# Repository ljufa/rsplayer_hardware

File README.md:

# RSPlayer Hardware

This repository contains the hardware design files for the RSPlayer project, a high-quality audio player. The designs are created in KiCad.

## Design Philosophy

This hardware design prioritizes **modularity** and **DIY-friendliness**. The goal is to provide a flexible platform where enthusiasts can easily swap components, upgrade specific subsystems (like power regulators or output stages), and experiment with different configurations. This open architecture encourages users to tweak the design, test new ideas, and continuously improve the audio performance to match their personal preferences.

## Boards
This repository is structured into several directories, each containing a specific board or a set of related files:

- **control_board_with_amanero**: A control board featuring an Amanero Combo768 USB interface.
- **lpf_ak4497**: Low-pass filter boards designed for the AK4497 DAC datasheet schematics. It includes designs for both `dual` and `dual_mono` configurations.
- [**LT3045_breakout**](https://github.com/PatrickBaus/LT3045_breakout.git): A modular breakout board for LT3042/LT3045 ultra-low noise regulators, used as drop-in replacements for 78xx series regulators.
- [**rsplayer_hardware_docs_private**](https://github.com/ljufa/rsplayer_hardware_docs_private.git): Contains external datasheets for various components used in the project. (this is private due to copyright)
- **MyLibrary.pretty**: A custom KiCad footprint library for this project.

## Features & Benefits

### Core Control & Interface
*   **MCU:** Powered by the **Raspberry Pi Pico (RP2040)**, providing robust system management, user interface control, and configuration logic. [**Firmware is here**](https://github.com/ljufa/rsplayer_firmware.git). 
*   **USB Audio:** Dedicated socket for **Amanero Combo384/Combo768** USB interfaces, supporting high-resolution PCM and DSD playback.
*   **User Interface:** Supports a Rotary Encoder for volume/navigation, IR Receiver (TSOP312) for remote control, and headers for LCD/OLED display integration.

### High-Fidelity Audio Design
*   **Galvanic Isolation:** Full isolation between the digital control logic (Pico/USB) and the sensitive DAC/Audio circuitry. Uses high-speed isolators (e.g., IL715E, ADuM1250) to eliminate ground loops and prevent digital noise from affecting audio quality.
*   **Hardware Muting:** Relay-based output muting protection to prevent audible pops and clicks during power cycles or sample rate changes.
*   **I2S Source Switching:** Features an intelligent I2S switching circuit using dual **74AC573** Octal Latches. This setup acts as a high-speed multiplexer, allowing seamless selection between the **Amanero USB interface (Source B)** and the **Optical/TOSLINK Input (Source A)**, controlled directly by the Raspberry Pi Pico.
*   **I2S & DSD Support:** Native handling of I2S and DSD signals routed directly to the DAC interface.

### Advanced Power Management
*   **Ultra-Low Noise Regulation:** Critically sensitive DAC stages are powered by modular **LT3042/LT3045** regulators. These are implemented as separate breakout boards (based on the `LT3045_breakout` design) acting as high-performance drop-in replacements for standard regulators, providing industry-leading low noise (0.8µVrms) and ultra-high PSRR.
*   **Multi-Rail Linear PSU:** On-board rectification and regulation generating separate clean rails for digital (3.3V), analog, and op-amp stages.
*   **Smart Power Control:** Relay-controlled AC mains switching allows for standby modes and remote power-on capabilities.

## Schematics

## PCB

## Future Roadmap
The project is evolving to become a universal high-fidelity audio platform. Planned improvements include:
*   **Expanded Interface Support:** Adding compatibility for additional **USB-to-I2S** boards beyond the Amanero series.
*   **Universal DAC Support:** Developing adapters and firmware logic to support a wider variety of **DAC chips and boards** (e.g., ESS Sabre, Burr-Brown), allowing users to choose their preferred sound signature.

## Related Projects
The RSPlayer is a multi-repository project:

- [**rsplayer**](https://github.com/ljufa/rsplayer.git): The main music player software running on PC or SBC.
- [**rsplayer_firmware**](https://github.com/ljufa/rsplayer_firmware.git): Firmware for MCU on this board. 

## License
This project is licensed under the MIT License. See the [LICENSE](LICENSE) file for details.

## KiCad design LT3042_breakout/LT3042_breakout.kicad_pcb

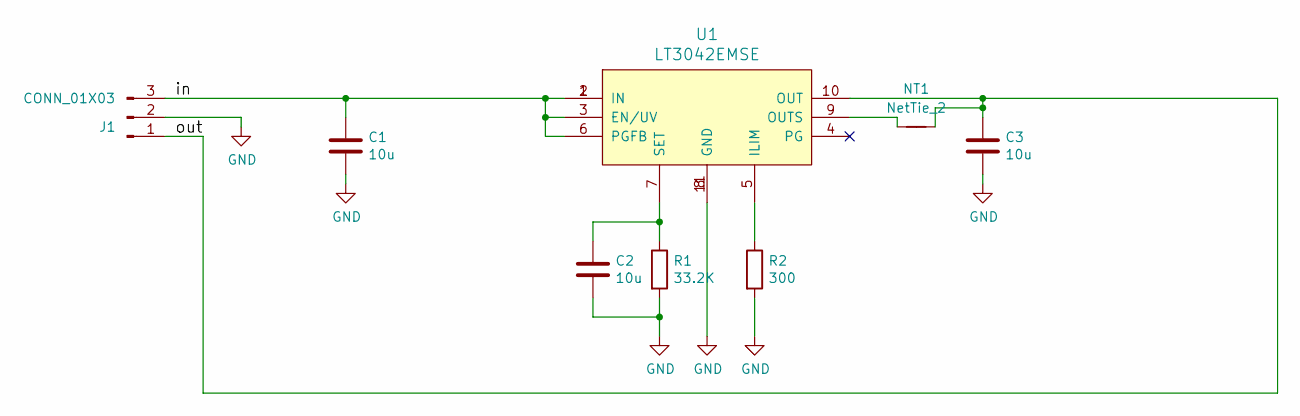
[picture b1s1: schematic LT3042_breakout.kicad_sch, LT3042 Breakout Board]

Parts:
C1, C2, C3: 10u; C_0603_1608Metric
J1: CONN_01X03; PinHeader_1x03_P2.54mm_Horizontal
NT1: NetTie_2; NetTie-2_SMD_Pad0.2mm
R1: 33.2K; R_0603_1608Metric
R2: 300; R_0603_1608Metric
U1: LT3042EMSE; MSOP-10-1EP_3x3mm_P0.5mm_EP1.68x1.88mm_ThermalVias

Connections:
/in: C1.1, J1.3, U1.1 (IN), U1.2 (IN), U1.3 (EN/UV), U1.6 (PGFB)
/out: C3.1, J1.1, NT1.2, U1.10 (OUT)
GND: C1.2, C2.2, C3.2, J1.2, R1.2, R2.2, U1.8 (GND), U1.11
unnamed: R2.1, U1.5 (ILIM)
unnamed: NT1.1, U1.9 (OUTS)
unnamed: C2.1, R1.1, U1.7 (SET)

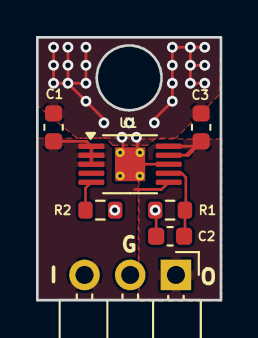
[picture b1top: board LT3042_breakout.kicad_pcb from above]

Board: 2 copper layers, 10.2 x 14.6 mm, 8 parts (0 on the bottom side), 6 nets.

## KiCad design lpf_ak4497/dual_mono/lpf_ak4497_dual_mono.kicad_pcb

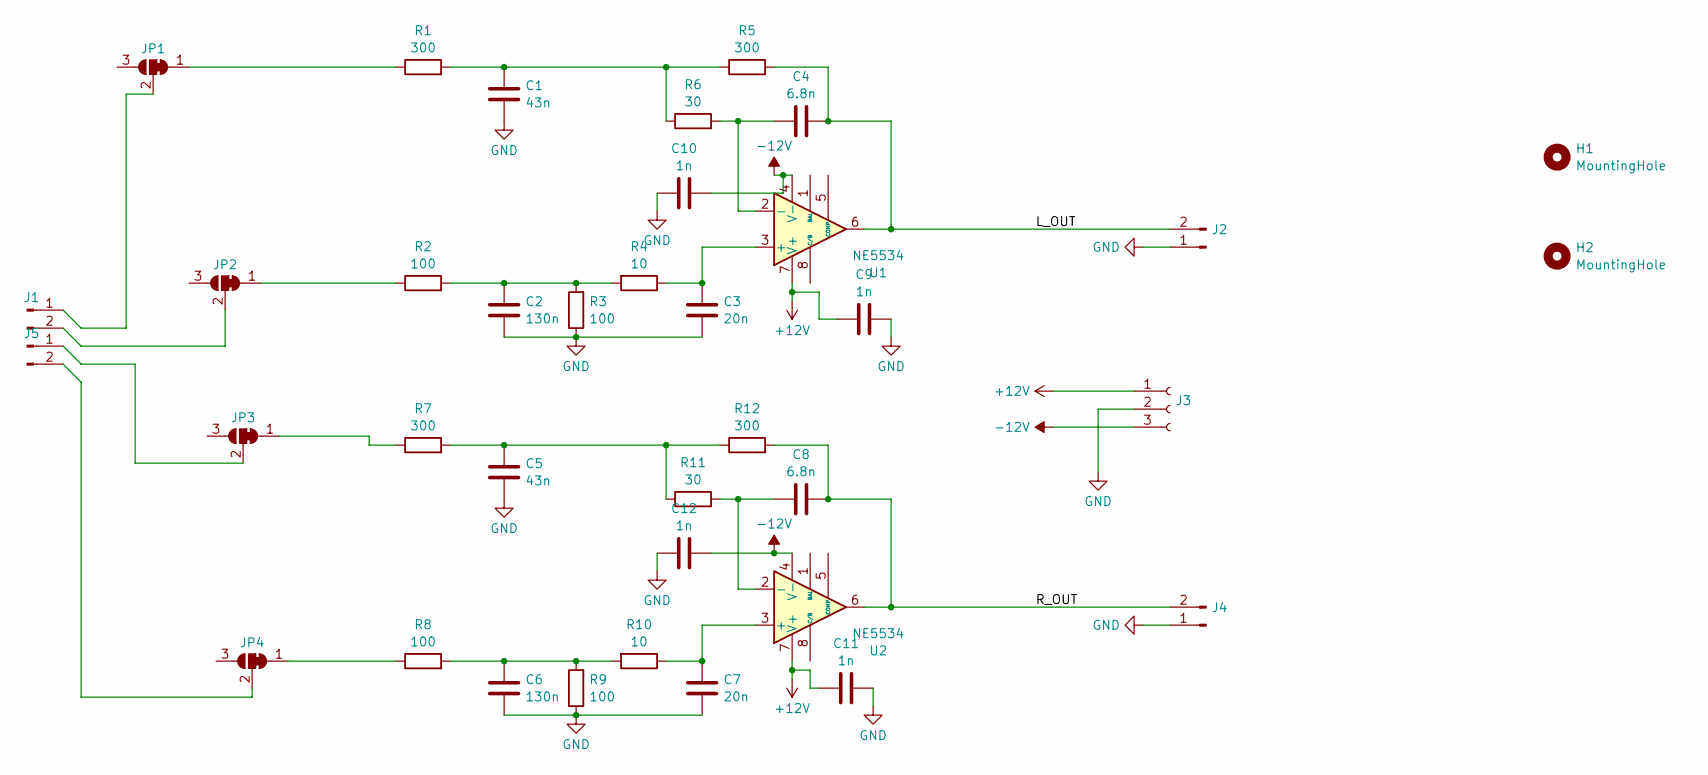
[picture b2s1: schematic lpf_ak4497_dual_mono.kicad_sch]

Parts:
C1, C5: 43n; C_1206_3216Metric_Pad1.33x1.80mm_HandSolder
C2, C6: 130n; C_1206_3216Metric_Pad1.33x1.80mm_HandSolder
C3, C7: 20n; C_1206_3216Metric_Pad1.33x1.80mm_HandSolder
C4, C8: 6.8n; C_1206_3216Metric_Pad1.33x1.80mm_HandSolder
C9, C10, C11, C12: 1n; C_0603_1608Metric_Pad1.08x0.95mm_HandSolder
H1, H2: MountingHole; MountingHole_3.2mm_M3
J1, J2, J4, J5: Conn_01x02_Pin; PinHeader_1x02_P2.54mm_Vertical
J3: Conn_01x03_Socket; PinHeader_1x03_P2.54mm_Vertical
JP1, JP2, JP3, JP4: SolderJumper-3_P1.3mm_Bridged2Bar12_RoundedPad1.0x1.5mm
R1, R5, R7, R12: 300; R_1206_3216Metric_Pad1.30x1.75mm_HandSolder
R2, R3, R8, R9: 100; R_1206_3216Metric_Pad1.30x1.75mm_HandSolder
R4, R10: 10; R_1206_3216Metric_Pad1.30x1.75mm_HandSolder
R6, R11: 30; R_1206_3216Metric_Pad1.30x1.75mm_HandSolder
U1, U2: NE5534; DIP-8_W7.62mm_Socket

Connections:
+12V: C9.2, C11.2, J3.1, U1.7 (V+), U2.7 (V+)
-12V: C10.1, C12.1, J3.3, U1.4 (V-), U2.4 (V-)
/L_OUT: C4.2, J2.2, R5.2, U1.6
/R_OUT: C8.2, J4.2, R12.2, U2.6
GND: C1.2, C2.2, C3.2, C5.2, C6.2, C7.2, C9.1, C10.2, C11.1, C12.2, J2.1, J3.2, J4.1, R3.1, R9.1
unnamed: C1.1, R1.2, R5.1, R6.1
unnamed: C2.1, R2.2, R3.2, R4.2
unnamed: C5.1, R7.2, R11.1, R12.1
unnamed: C6.1, R8.2, R9.2, R10.2
unnamed: J1.1, JP1.2 (C)
unnamed: J1.2, JP2.2 (C)
unnamed: J5.1, JP3.2 (C)
unnamed: J5.2, JP4.2 (C)
unnamed: JP1.1 (A), R1.1
unnamed: JP2.1 (A), R2.1
unnamed: JP3.1 (A), R7.1
unnamed: JP4.1 (A), R8.1
unnamed: C3.1, R4.1, U1.3 (+)
unnamed: C4.1, R6.2, U1.2 (-)
unnamed: C7.1, R10.1, U2.3 (+)
unnamed: C8.1, R11.2, U2.2 (-)

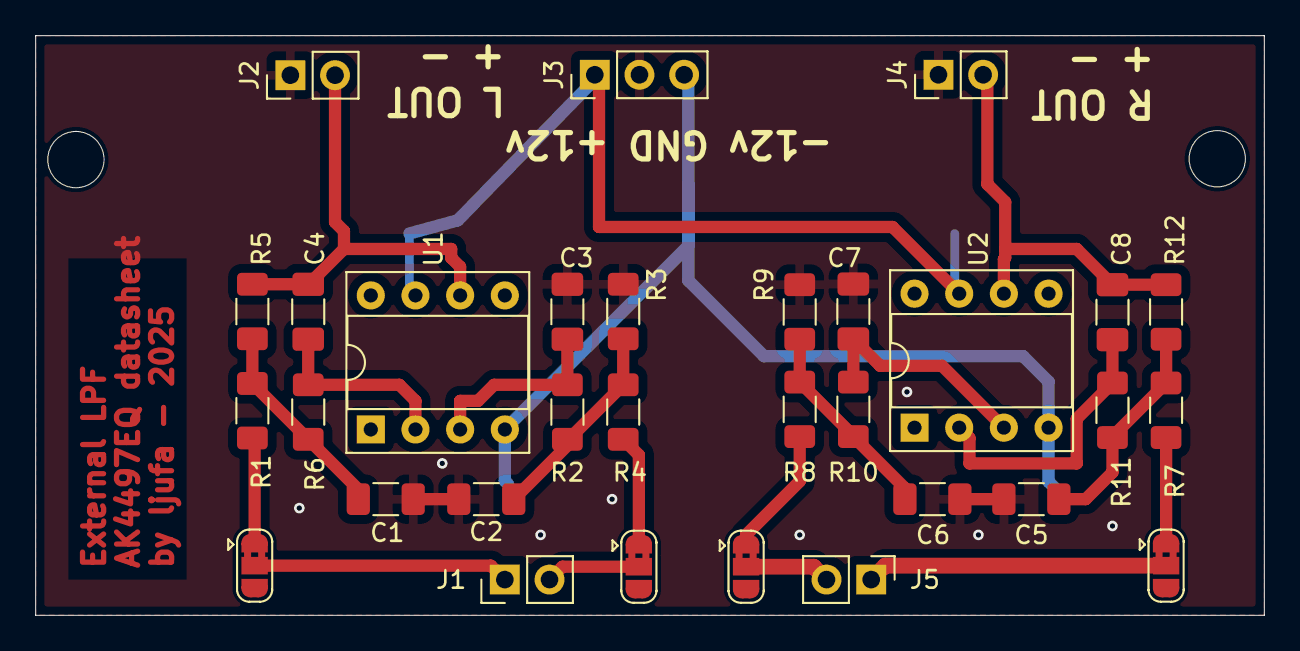
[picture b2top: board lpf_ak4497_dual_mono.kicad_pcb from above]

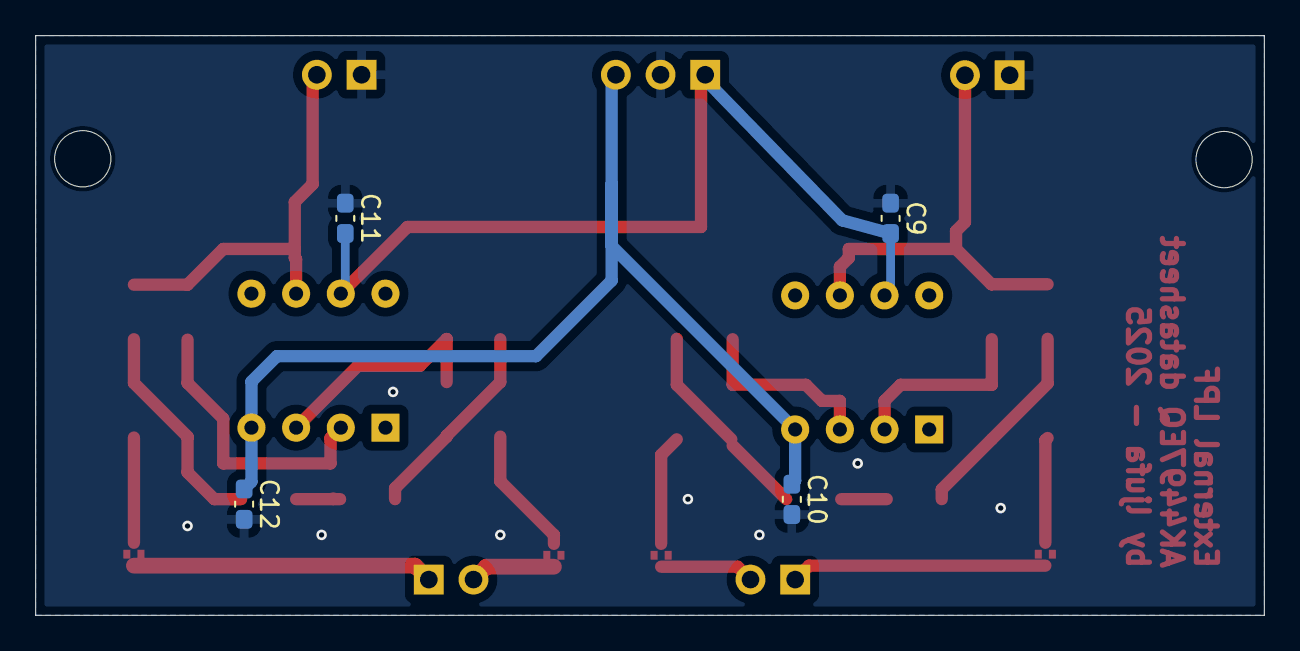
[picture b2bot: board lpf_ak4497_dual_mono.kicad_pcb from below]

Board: 2 copper layers, 69.9 x 33.0 mm, 37 parts (4 on the bottom side), 21 nets.

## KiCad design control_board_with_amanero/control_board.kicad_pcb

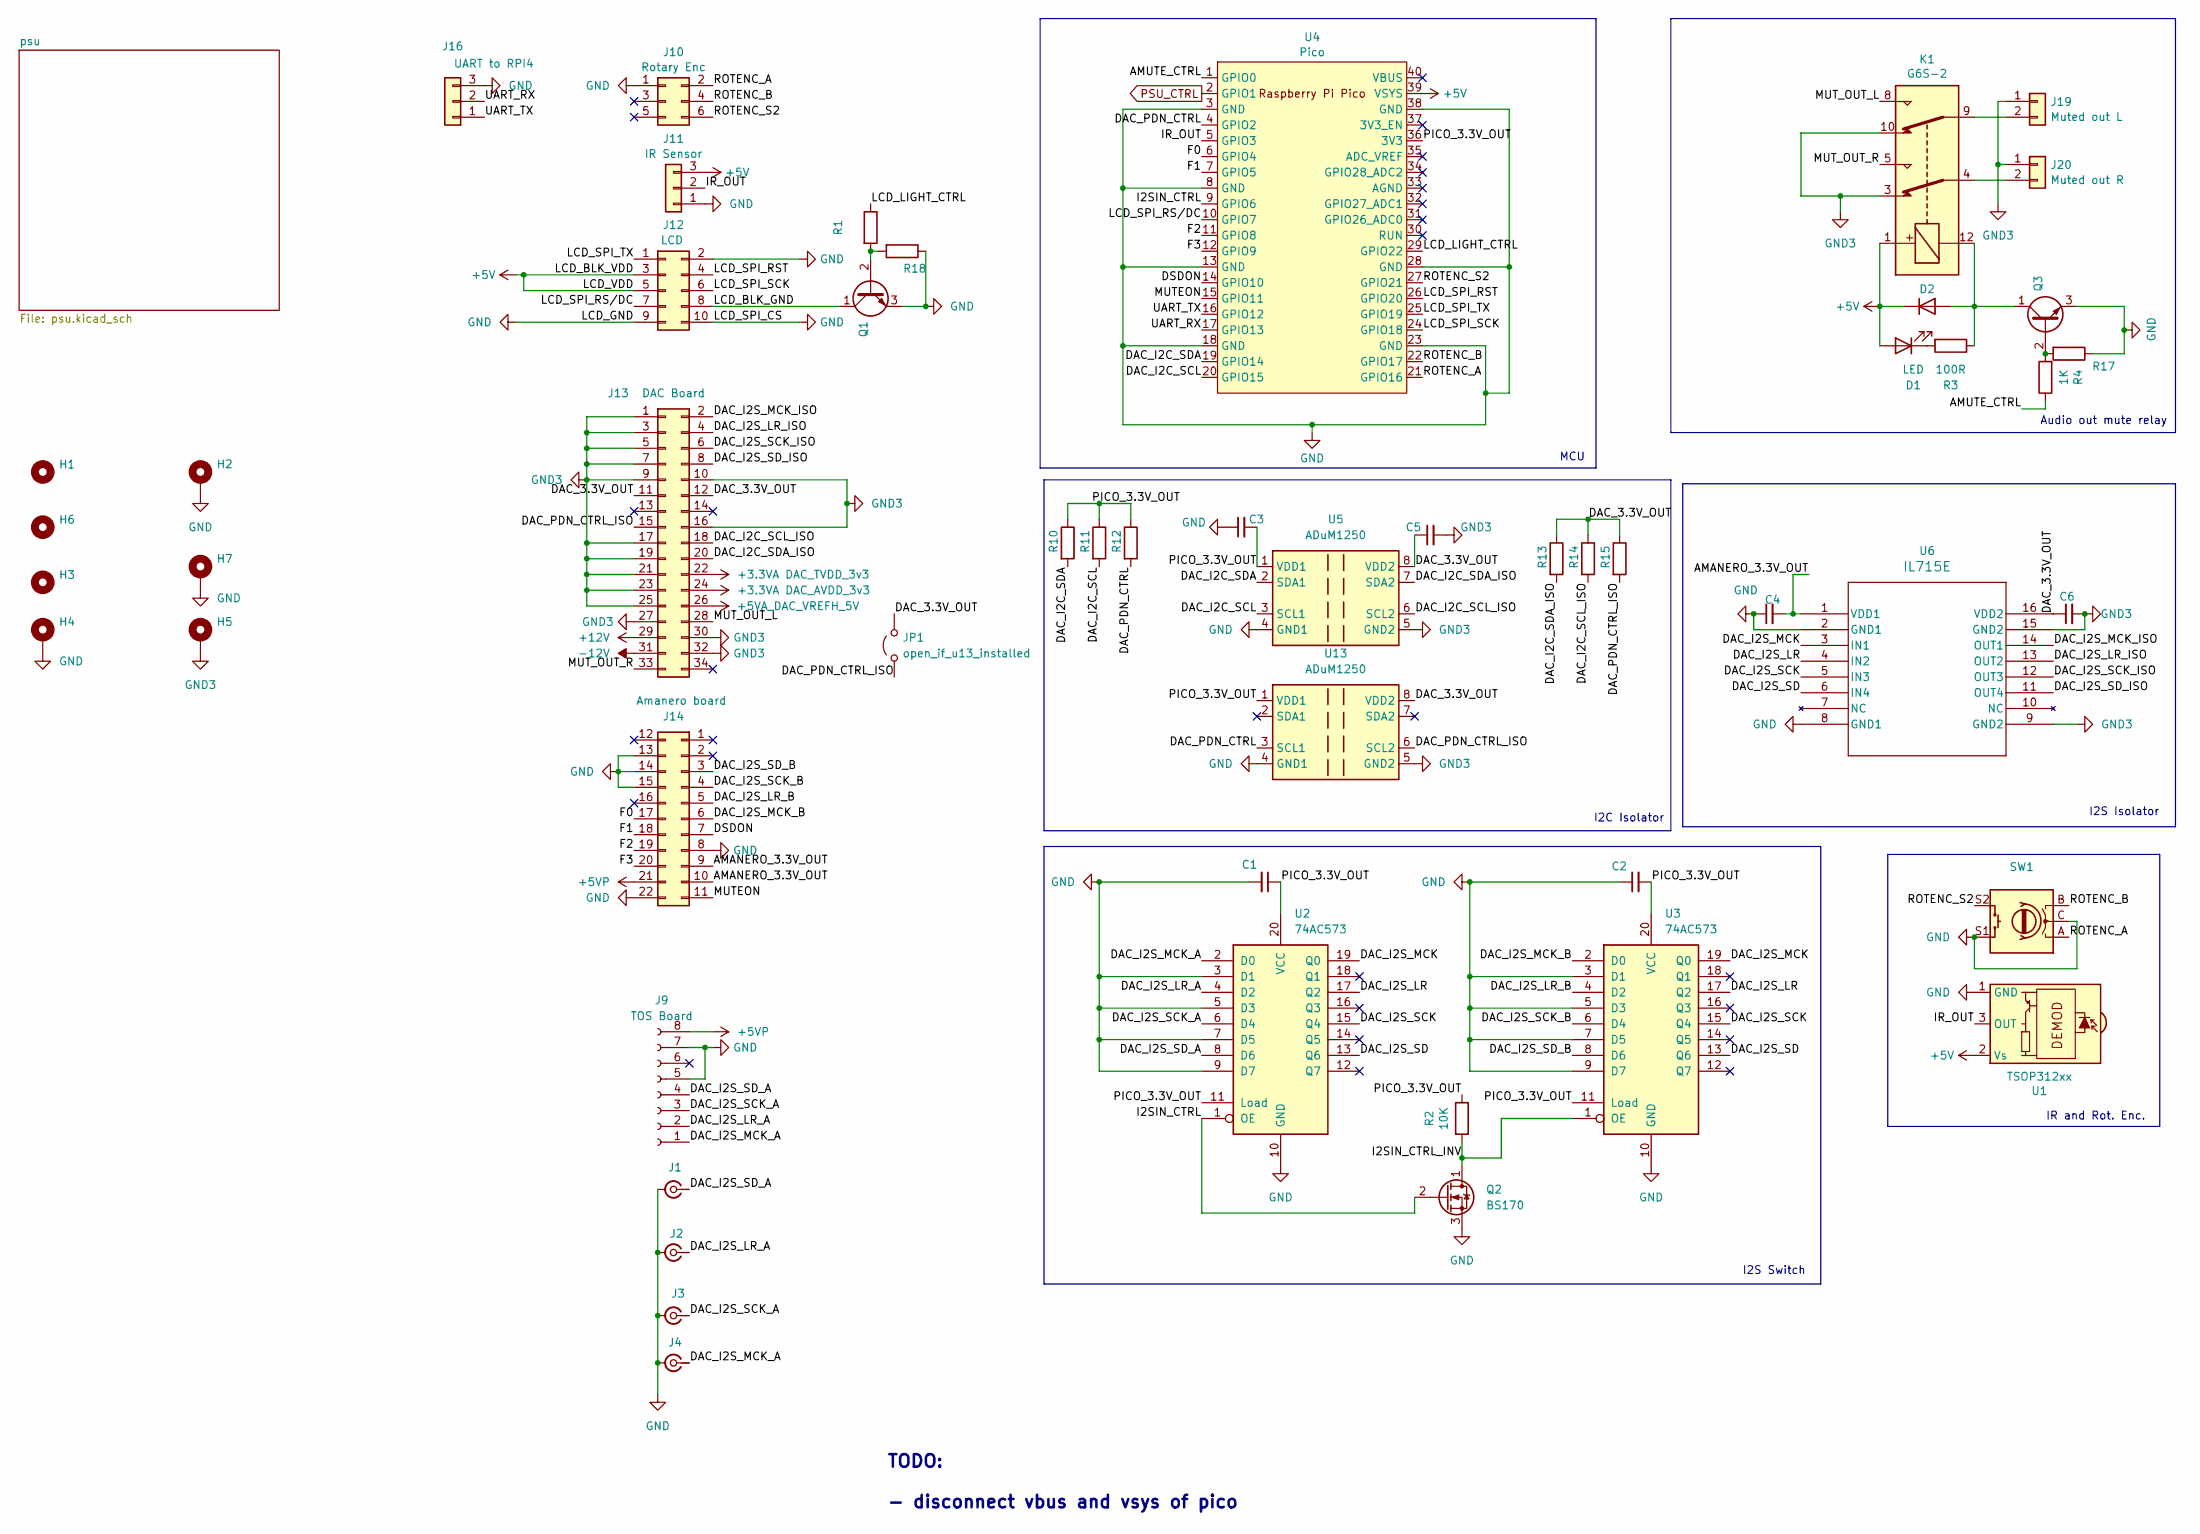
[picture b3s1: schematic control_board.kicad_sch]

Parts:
C1, C2, C3, C4, C5, C6: 0.1u; C_1206_3216Metric_Pad1.33x1.80mm_HandSolder
D1: LED; LED_1206_3216Metric
D2: 1N4004; D_MicroMELF_Handsoldering
H1, H3, H6: MountingHole_3.2mm_M3
H2, H4, H5, H7: MountingHole_3.2mm_M3_Pad_TopBottom
J1, J2, J3, J4: Conn_Coaxial_Small; U.FL_Molex_MCRF_73412-0110_Vertical
J9: TOS Board; tosInputBoard
J10: Rotary Enc; IDC-Header_2x03_P2.54mm_Vertical
J11: IR Sensor; PinHeader_1x03_P2.54mm_Vertical
J12: LCD; IDC-Header_2x05_P2.54mm_Vertical
J13: DAC Board; diyinkhak4490+4497board
J14: Amanero board; Amanero Combo768
J16: UART to RPI4; PinSocket_1x03_P2.54mm_Vertical
J19: Muted out L; PinHeader_1x02_P2.54mm_Vertical
J20: Muted out R; PinHeader_1x02_P2.54mm_Vertical
JP1: open_if_u13_installed; SolderJumper-2_P1.3mm_Open_Pad1.0x1.5mm
K1: G6S-2; Relay_DPDT_Omron_G6S-2
Q1, Q3: BC547; TO-92_Inline
Q2: BS170; TO-92_Inline
R1, R4: 1K; R_1206_3216Metric_Pad1.30x1.75mm_HandSolder
R2, R10, R11, R12, R13, R14, R15, R17, R18: 10K; R_1206_3216Metric_Pad1.30x1.75mm_HandSolder
R3: 100R; R_1206_3216Metric
SW1: RotaryEncoder_Switch
U1: TSOP312xx; Vishay_CAST-3Pin
U2, U3: 74AC573; SOIC-20W_7.5x12.8mm_P1.27mm
U4: Pico; RaspberryPi_Pico_Common_THT
U5, U13: ADuM1250; SOIC-8_3.9x4.9mm_P1.27mm
U6: IL715E; SOIC16_WIDE_NVE

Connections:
+3.3VA DAC_AVDD_3v3: J13.24; also elsewhere on the board
+3.3VA DAC_TVDD_3v3: J13.22; also elsewhere on the board
+5V: D1.2 (A), D2.1 (K), J11.3, J12.3, J12.5, K1.1, U4.39 (VSYS); also elsewhere on the board
+5VA_DAC_VREFH_5V: J13.26; also elsewhere on the board
+5VP: J9.8, J14.21; also elsewhere on the board
+12V: J13.29; also elsewhere on the board
-12V: J13.31; also elsewhere on the board
/AMANERO_3.3V_OUT: C4.2, J14.9, J14.10, U6.1 (VDD1)
/AMUTE_CTRL: R4.1, U4.1 (GPIO0)
/DAC_3.3V_OUT: C5.1, C6.1, J13.11, J13.12, JP1.2 (B), R13.1, R14.1, R15.1, U5.8 (VDD2), U6.16 (VDD2), U13.8 (VDD2)
/DAC_I2C_SCL: R11.2, U4.20 (GPIO15), U5.3 (SCL1)
/DAC_I2C_SCL_ISO: J13.18, R14.2, U5.6 (SCL2)
/DAC_I2C_SDA: R10.2, U4.19 (GPIO14), U5.2 (SDA1)
/DAC_I2C_SDA_ISO: J13.20, R13.2, U5.7 (SDA2)
/DAC_I2S_LR: U2.17 (Q2), U3.17 (Q2), U6.4 (IN2)
/DAC_I2S_LR_A: J2.1 (In), J9.2, U2.4 (D2)
/DAC_I2S_LR_B: J14.5, U3.4 (D2)
/DAC_I2S_LR_ISO: J13.4, U6.13 (OUT2)
/DAC_I2S_MCK: U2.19 (Q0), U3.19 (Q0), U6.3 (IN1)
/DAC_I2S_MCK_A: J4.1 (In), J9.1, U2.2 (D0)
/DAC_I2S_MCK_B: J14.6, U3.2 (D0)
/DAC_I2S_MCK_ISO: J13.2, U6.14 (OUT1)
/DAC_I2S_SCK: U2.15 (Q4), U3.15 (Q4), U6.5 (IN3)
/DAC_I2S_SCK_A: J3.1 (In), J9.3, U2.6 (D4)
/DAC_I2S_SCK_B: J14.4, U3.6 (D4)
/DAC_I2S_SCK_ISO: J13.6, U6.12 (OUT3)
/DAC_I2S_SD: U2.13 (Q6), U3.13 (Q6), U6.6 (IN4)
/DAC_I2S_SD_A: J1.1 (In), J9.4, U2.8 (D6)
/DAC_I2S_SD_B: J14.3, U3.8 (D6)
/DAC_I2S_SD_ISO: J13.8, U6.11 (OUT4)
/DAC_PDN_CTRL: R12.2, U4.4 (GPIO2), U13.3 (SCL1)
/DAC_PDN_CTRL_ISO: J13.15, JP1.1 (A), R15.2, U13.6 (SCL2)
/DSDON: J14.7, U4.14 (GPIO10)
/F0: J14.17, U4.6 (GPIO4)
/F1: J14.18, U4.7 (GPIO5)
/F2: J14.19, U4.11 (GPIO8)
/F3: J14.20, U4.12 (GPIO9)
/I2SIN_CTRL: Q2.2 (G), U2.1 (OE), U4.9 (GPIO6)
/I2SIN_CTRL_INV: Q2.1 (D), R2.2, U3.1 (OE)
/IR_OUT: J11.2, U4.5 (GPIO3)
/LCD_BLK_GND: J12.8, Q1.1 (C)
/LCD_LIGHT_CTRL: R1.1, U4.29 (GPIO22)
/LCD_SPI_RST: J12.4, U4.26 (GPIO20)
/LCD_SPI_RS/DC: J12.7, U4.10 (GPIO7)
/LCD_SPI_SCK: J12.6, U4.24 (GPIO18)
/LCD_SPI_TX: J12.1, U4.25 (GPIO19)
/MUTEON: J14.11, U4.15 (GPIO11)
/MUT_OUT_L: J13.28, K1.8
/MUT_OUT_R: J13.33, K1.5
/PICO_3.3V_OUT: C1.1, C2.2, C3.2, R2.1, R10.1, R11.1, R12.1, U2.11 (Load), U2.20 (VCC), U3.11 (Load), U3.20 (VCC), U4.36 (3V3), U5.1 (VDD1), U13.1 (VDD1)
/ROTENC_A: J10.2, U4.21 (GPIO16)
/ROTENC_B: J10.4, SW1.B, U4.22 (GPIO17); also elsewhere on the board
/ROTENC_S2: J10.6, SW1.S2, U4.27 (GPIO21); also elsewhere on the board
/UART_RX: J16.2, U4.17 (GPIO13)
/UART_TX: J16.1, U4.16 (GPIO12)
GND: C1.2, C2.1, C3.1, C4.1, H2.1, H4.1, H7.1, J1.2 (Ext), J2.2 (Ext), J3.2 (Ext), J4.2 (Ext), J9.5, J9.7, J10.1, J11.1, J12.2, J12.9, J12.10, J14.8, J14.13, J14.14, J14.15, J14.22, J16.3, Q1.3 (E), Q2.3 (S), Q3.3 (E), R17.1, R18.1, U2.3 (D1), U2.5 (D3), U2.7 (D5), U2.9 (D7), U2.10 (GND), U3.3 (D1), U3.5 (D3), U3.7 (D5), U3.9 (D7), U3.10 (GND), U4.3 (GND), U4.8 (GND), U4.13 (GND), U4.18 (GND), U4.23 (GND), U4.28 (GND), U4.38 (GND), U5.4 (GND1), U6.2 (GND1), U6.8 (GND1), U13.4 (GND1); also elsewhere on the board
GND3: C5.2, C6.2, H5.1, J13.1, J13.3, J13.5, J13.7, J13.9, J13.10, J13.16, J13.17, J13.19, J13.21, J13.23, J13.25, J13.27, J13.30, J13.32, J19.1, J20.1, K1.3, K1.10, U5.5 (GND2), U6.9 (GND2), U6.15 (GND2), U13.5 (GND2); also elsewhere on the board
unnamed: D1.1 (K), R3.2
unnamed: D2.2 (A), K1.12, Q3.1 (C), R3.1
unnamed: J19.2, K1.9
unnamed: J20.2, K1.4
unnamed: Q1.2 (B), R1.2, R18.2
unnamed: Q3.2 (B), R4.2, R17.2
PSU_CTRL: U4.2 (GPIO1); also elsewhere on the board

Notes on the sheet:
IR and Rot. Enc.
I2C Isolator
Audio out mute relay
MCU
I2S Isolator
I2S Switch
TODO: - disconnect vbus and vsys of pico

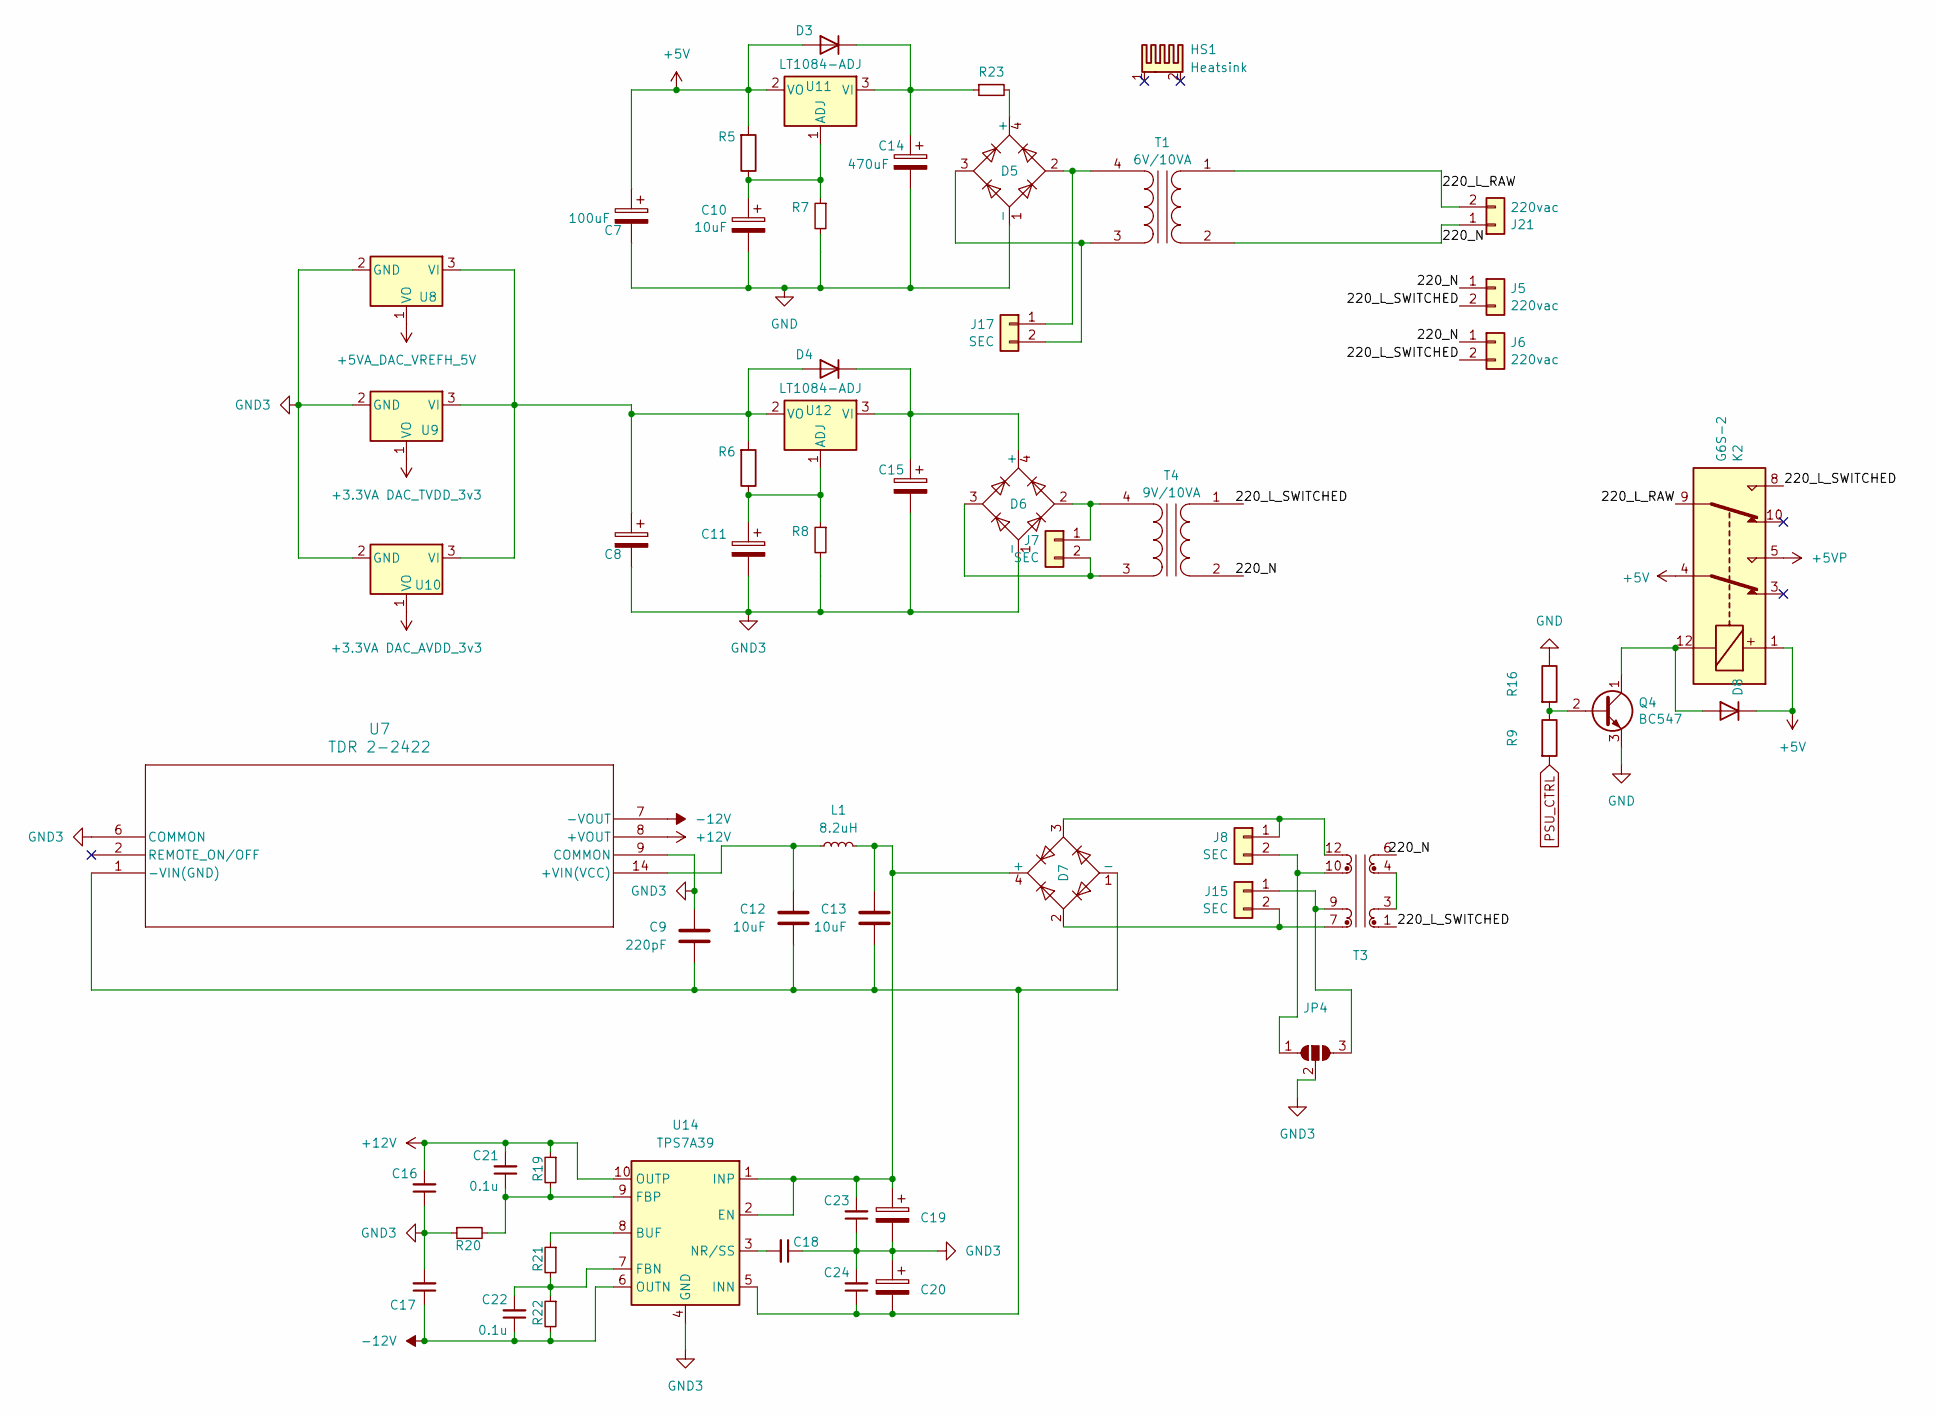
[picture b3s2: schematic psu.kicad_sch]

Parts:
C7, C8: 100uF; CP_Radial_D8.0mm_P3.50mm
C9: 220pF; C_1206_3216Metric_Pad1.33x1.80mm_HandSolder
C10, C11, C12, C13: 10uF; CP_Radial_D5.0mm_P2.00mm
C14, C15: 470uF; CP_Radial_D13.0mm_P5.00mm
C16, C17: Value=22uF; C_1206_3216Metric_Pad1.33x1.80mm_HandSolder
C18: Value=10nF; C_1206_3216Metric_Pad1.33x1.80mm_HandSolder
C19, C20: Value=33uF Rser=350m; CP_EIA-3528-21_Kemet-B_HandSolder
C21, C22, C23, C24: 0.1u; C_1206_3216Metric_Pad1.33x1.80mm_HandSolder
D3, D4, D8: 1N4004; D_MicroMELF_Handsoldering
D5, D6, D7: B80C3x00-2200A; Diode_Bridge_Vishay_GBU
HS1: Heatsink; Heatsink_Fischer_SK104-STC-STIC_35x13mm_2xDrill2.5mm
J5, J6, J21: 220vac; TerminalBlock_Philmore_TB132_1x02_P5.00mm_Horizontal
J7, J8, J15, J17: SEC; TerminalBlock_Philmore_TB132_1x02_P5.00mm_Horizontal
JP4: SolderJumper_3_Open; SolderJumper-3_P2.0mm_Open_TrianglePad1.0x1.5mm_NumberLabels
K2: G6S-2; Relay_DPDT_Omron_G6S-2
L1: 8.2uH; L_SXN_SMDRI73
Q4: BC547; TO-92_Inline
R5, R6: 100R; R_1206_3216Metric_Pad1.30x1.75mm_HandSolder
R7: 300R; R_1206_3216Metric_Pad1.30x1.75mm_HandSolder
R8: 470R; R_1206_3216Metric_Pad1.30x1.75mm_HandSolder
R9: 1K; R_1206_3216Metric_Pad1.30x1.75mm_HandSolder
R16: 10K; R_1206_3216Metric_Pad1.30x1.75mm_HandSolder
R19: 90.9K; R_1206_3216Metric_Pad1.30x1.75mm_HandSolder
R20, R21: 10k; R_1206_3216Metric_Pad1.30x1.75mm_HandSolder
R22: 100k; R_1206_3216Metric_Pad1.30x1.75mm_HandSolder
R23: 0R; R_Axial_DIN0516_L15.5mm_D5.0mm_P7.62mm_Vertical
T1: 6V/10VA; MYRRA_44266
T3: Triad_VPP16-310; Transformer_Murata_PL10-28-130B
T4: 9V/10VA; MYRRA_44266
U7: TDR 2-2422; TDR 2 DUAL_TRP
U8, U9, U10: lt3042_breakout; TO-220-3_Vertical
U11, U12: LT1084-ADJ; TO-220-3_Vertical
U14: TPS7A39; Texas_S-PVSON-N10_ThermalVias

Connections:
+3.3VA DAC_AVDD_3v3: U10.1 (VO); also elsewhere on the board
+3.3VA DAC_TVDD_3v3: U9.1 (VO); also elsewhere on the board
+5V: C7.1, D3.2 (A), D8.1 (K), K2.1, K2.4, R5.2, U11.2 (VO); also elsewhere on the board
+5VA_DAC_VREFH_5V: U8.1 (VO); also elsewhere on the board
+5VP: K2.5; also elsewhere on the board
+12V: C16.2, C21.2, R19.1, U7.8 (+VOUT), U14.10 (OUTP); also elsewhere on the board
-12V: C17.1, C22.1, R22.2, U7.7 (-VOUT), U14.6 (OUTN); also elsewhere on the board
/psu/220_L_RAW: J21.2, K2.9, T1.1 (AA)
/psu/220_L_SWITCHED: J5.2, J6.2, K2.8, T3.1
/psu/220_N: J5.1, J6.1, J21.1, T1.2 (AB)
GND: C7.2, C10.2, C14.2, D5.1 (-), Q4.3 (E), R7.2, R16.1; also elsewhere on the board
GND3: C8.2, C9.1, C11.2, C15.2, C16.1, C17.2, C18.1, C19.2, C20.1, C23.1, C24.2, D6.1 (-), JP4.2 (C), R8.2, R20.1, U7.6 (COMMON), U7.9 (COMMON), U8.2 (GND), U9.2 (GND), U10.2 (GND), U14.4 (GND), U14.11 (GND); also elsewhere on the board
unnamed: C14.1, D3.1 (K), R23.1, U11.3 (VI)
unnamed: C8.1, D4.2 (A), R6.2, U8.3 (VI), U9.3 (VI), U10.3 (VI), U12.2 (VO)
unnamed: C15.1, D4.1 (K), D6.4 (+), U12.3 (VI)
unnamed: D5.4 (+), R23.2
unnamed: C13.1, C19.1, C23.2, D7.4 (+), L1.1, U14.1 (INP), U14.2 (EN)
unnamed: C9.2, C12.2, C13.2, C20.2, C24.1, D7.1 (-), U7.1 (-VIN(GND)), U14.5 (INN)
unnamed: D8.2 (A), K2.12, Q4.1 (C)
unnamed: D6.2, J7.1, T4.4 (SB)
unnamed: D6.3, J7.2, T4.3 (SA)
unnamed: D7.3, J8.1, T3.12
unnamed: J8.2, JP4.1 (A), T3.10
unnamed: J15.1, JP4.3 (B), T3.9
unnamed: D7.2, J15.2, T3.7
unnamed: D5.2, J17.1, T1.4 (SB)
unnamed: D5.3, J17.2, T1.3 (SA)
unnamed: Q4.2 (B), R9.1, R16.2
unnamed: T3.3, T3.4
unnamed: C12.1, L1.2, U7.14 (+VIN(VCC))
unnamed: C10.1, R5.1, R7.1, U11.1 (ADJ)
unnamed: C11.1, R6.1, R8.1, U12.1 (ADJ)
unnamed: R21.1, U14.8 (BUF)
unnamed: C22.2, R21.2, R22.1, U14.7 (FBN)
unnamed: C21.1, R19.2, R20.2, U14.9 (FBP)
unnamed: C18.2, U14.3 (NR/SS)
PSU_CTRL: R9.2; also elsewhere on the board

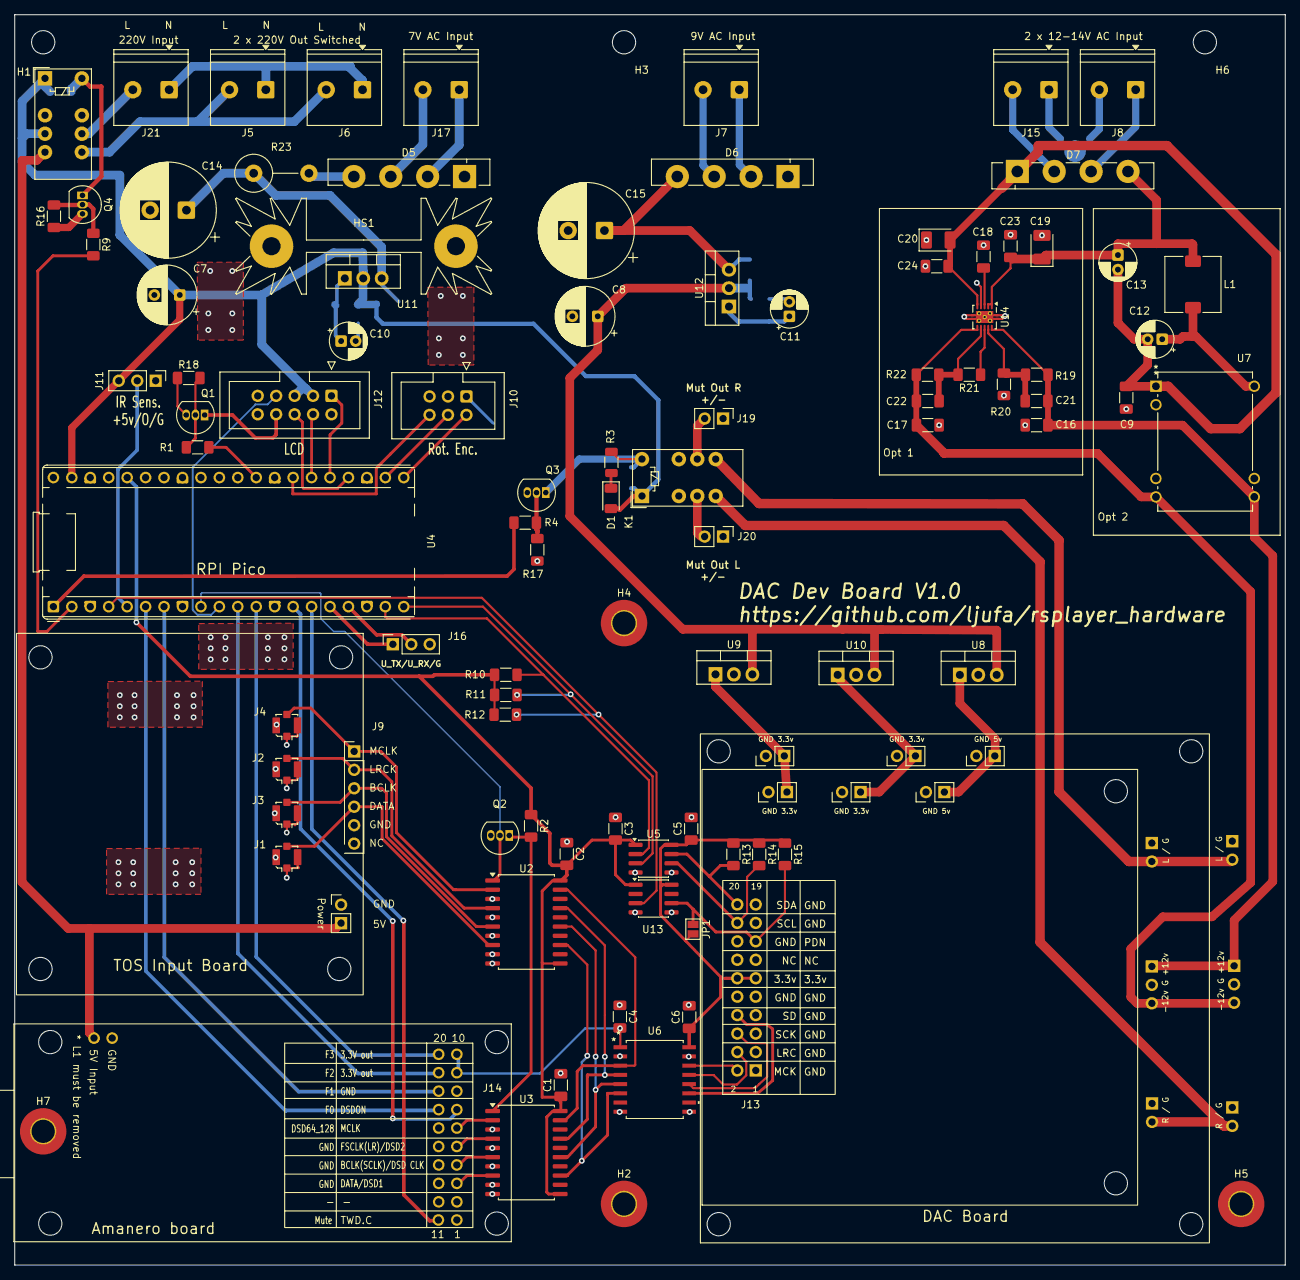
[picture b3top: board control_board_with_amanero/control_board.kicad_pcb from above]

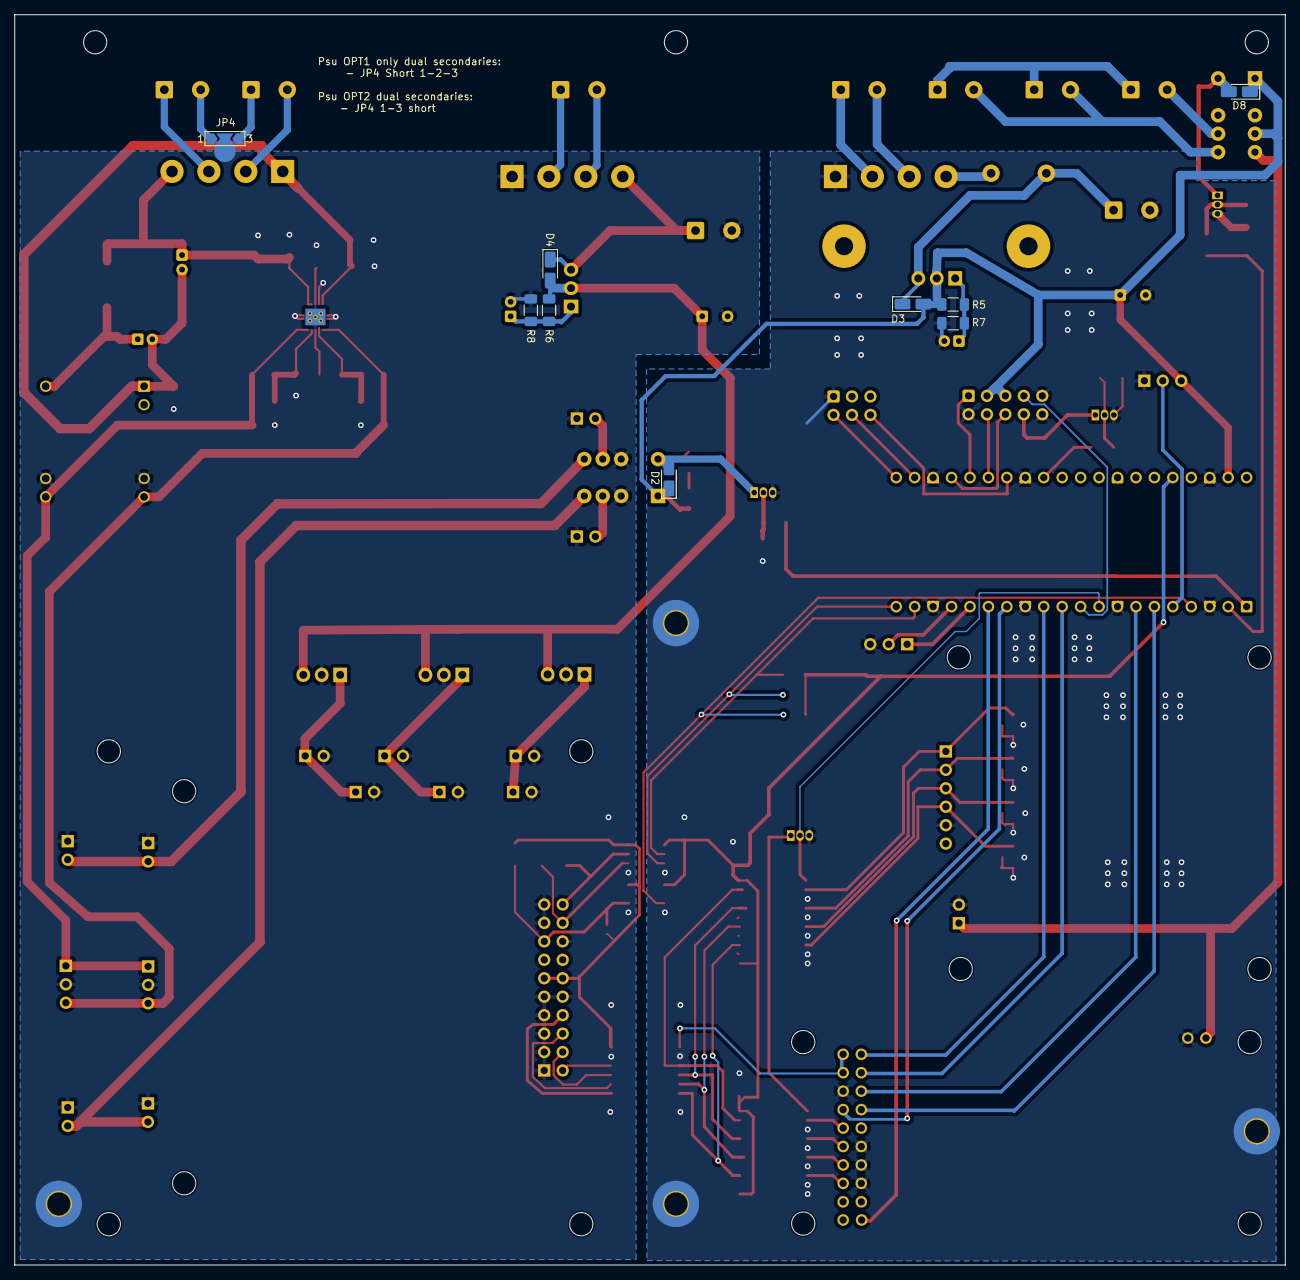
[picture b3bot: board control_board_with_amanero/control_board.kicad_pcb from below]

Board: 2 copper layers, 175.0 x 172.2 mm, 105 parts (9 on the bottom side), 90 nets.
